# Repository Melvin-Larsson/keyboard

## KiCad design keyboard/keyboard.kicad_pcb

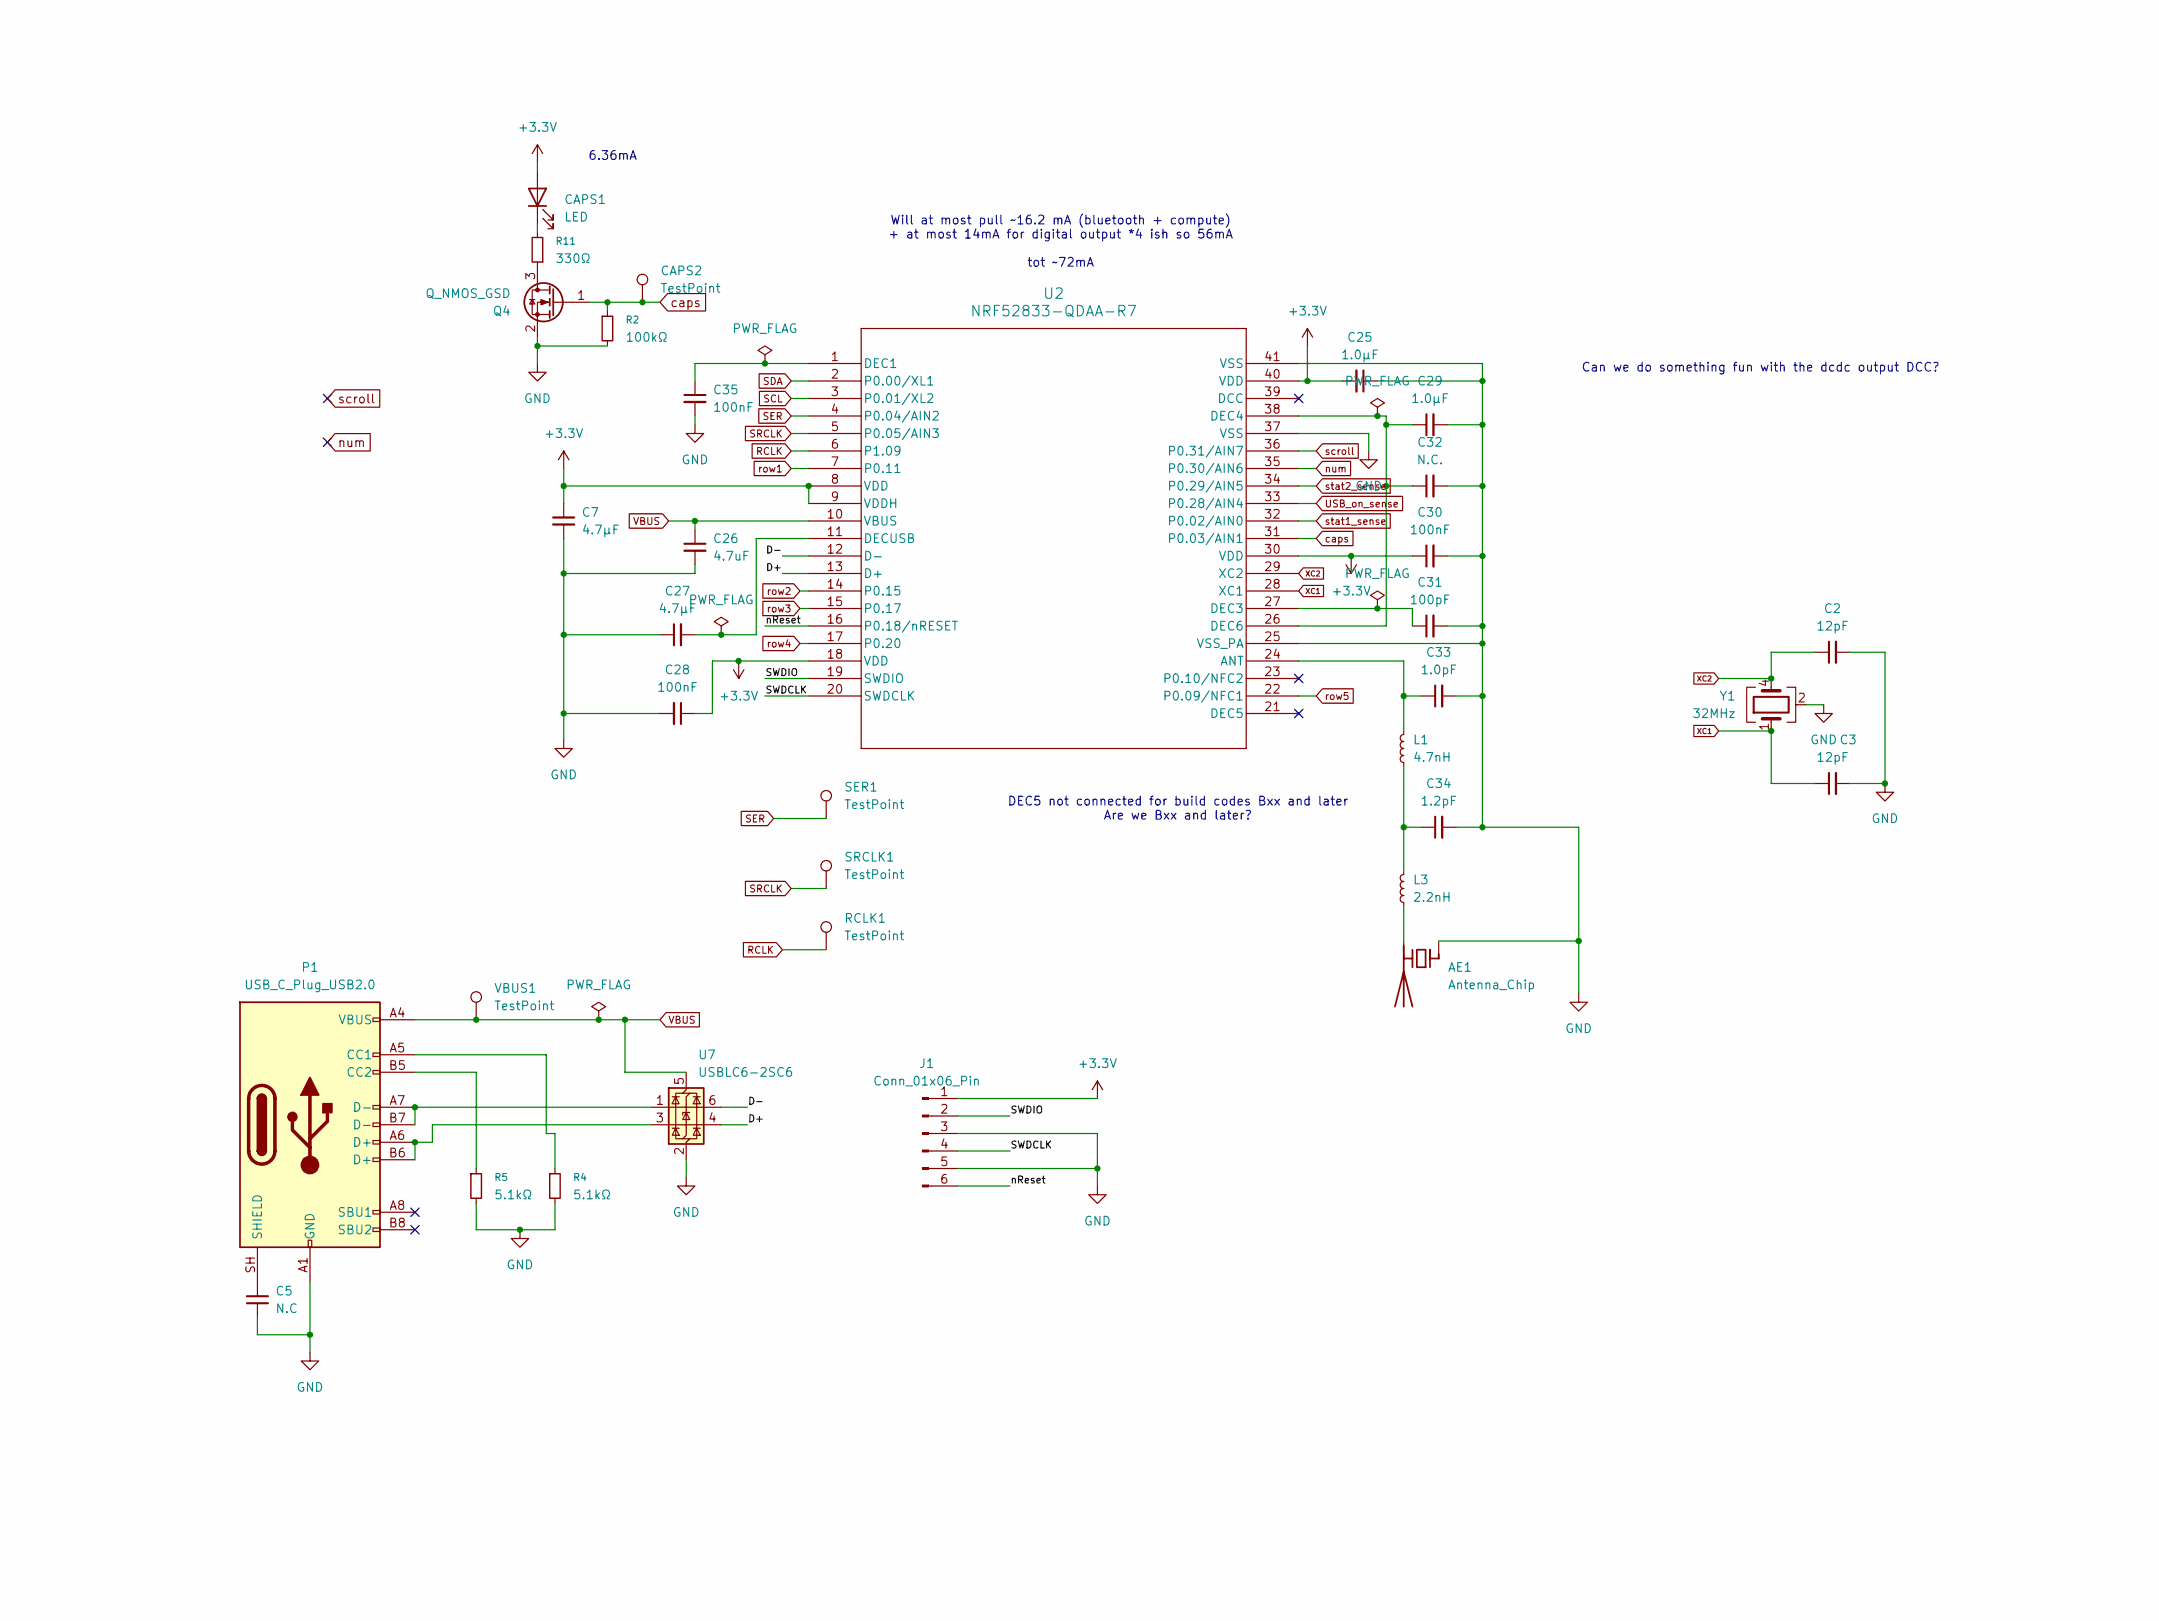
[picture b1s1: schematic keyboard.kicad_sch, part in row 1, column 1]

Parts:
AE1: Antenna_Chip; PCB-Antenna
C2, C3: 12pF; C_0201_0603Metric
C5: N.C; C_0603_1608Metric
C7, C27: 4.7μF; C_0603_1608Metric
C25, C29: 1.0μF; C_0402_1005Metric_small_silk
C26: 4.7uF; C_0603_1608Metric
C28, C30, C35: 100nF; C_0201_0603Metric
C31: 100pF; C_0201_0603Metric
C32: N.C.; C_0201_0603Metric
C33: 1.0pF; C_0201_0603Metric
C34: 1.2pF; C_0201_0603Metric
CAPS1: LED; LED_0603_1608Metric
CAPS2: TestPoint; TestPoint_THTPad_D2.0mm_Drill1.0mm_no_silk
J1: Conn_01x06_Pin; PinHeader_2x03_P2.54mm_Vertical
L1: 4.7nH; L_0201_0603Metric
L3: 2.2nH; L_0201_0603Metric
P1: USB_C_Plug_USB2.0; USB_C_Receptacle_G-Switch_GT-USB-7010ASV
Q4: Q_NMOS_GSD; SOT-23
R2: 100kΩ; R_0603_1608Metric
R4, R5: 5.1kΩ; R_0603_1608Metric
R11: 330Ω; R_0603_1608Metric
RCLK1: TestPoint; TestPoint_THTPad_D2.0mm_Drill1.0mm_no_silk
SER1: TestPoint; TestPoint_THTPad_D2.0mm_Drill1.0mm_no_silk
SRCLK1: TestPoint; TestPoint_THTPad_D2.0mm_Drill1.0mm_no_silk
U2: NRF52833-QDAA-R7; QFN40_5X5_DQ_NOR
U7: USBLC6-2SC6; SOT-23-6
VBUS1: TestPoint; TestPoint_THTPad_D2.0mm_Drill1.0mm_no_silk
Y1: 32MHz; Crystal_SMD_2016-4Pin_2.0x1.6mm

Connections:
+3.3V: C7.1, C25.2, C28.1, C30.1, CAPS1.2 (A), J1.1, U2.8 (VDD), U2.9 (VDDH), U2.18 (VDD), U2.30 (VDD), U2.40 (VDD); also elsewhere on the board
/D+: U2.13 (D+), U7.4 (I/O2)
/D-: U2.12 (D-), U7.6 (I/O1)
/SWDCLK: J1.4, U2.20 (SWDCLK)
/SWDIO: J1.2, U2.19 (SWDIO)
/nReset: J1.6, U2.16 (P0.18/nRESET)
GND: AE1.1 (FEED), C2.2, C3.2, C5.2, C7.2, C25.1, C26.2, C27.1, C28.2, C29.2, C30.2, C31.2, C32.2, C33.2, C34.2, C35.2, J1.3, J1.5, P1.A1 (GND), P1.A12 (GND), P1.B1 (GND), P1.B12 (GND), Q4.2 (S), R2.2, R4.2, R5.2, U2.25 (VSS_PA), U2.37 (VSS), U2.41 (VSS), U7.2 (GND), Y1.2 (G), Y1.3 (G); also elsewhere on the board
unnamed: AE1.2 (PCB_Trace), L3.1
unnamed: C34.1, L1.1, L3.2
unnamed: CAPS1.1 (K), R11.2
unnamed: P1.A5 (CC1), R4.1
unnamed: P1.B5 (CC2), R5.1
unnamed: P1.A6 (D+), P1.B6 (D+), U7.3 (I/O2)
unnamed: P1.A7 (D-), P1.B7 (D-), U7.1 (I/O1)
unnamed: C5.1, P1.SH (SHIELD)
unnamed: Q4.3 (D), R11.1
unnamed: C33.1, L1.2, U2.24 (ANT)
unnamed: C35.1, U2.1 (DEC1)
unnamed: C31.1, U2.27 (DEC3)
unnamed: C29.1, C32.1, U2.26 (DEC6), U2.38 (DEC4)
unnamed: C27.2, U2.11 (DECUSB)
RCLK: RCLK1.1 (1_1), U2.6 (P1.09); also elsewhere on the board
SCL: U2.3 (P0.01/XL2); also elsewhere on the board
SDA: U2.2 (P0.00/XL1); also elsewhere on the board
SER: SER1.1 (1_1), U2.4 (P0.04/AIN2); also elsewhere on the board
SRCLK: SRCLK1.1 (1_1), U2.5 (P0.05/AIN3); also elsewhere on the board
STAT1: U2.32 (P0.02/AIN0); also elsewhere on the board
STAT2: U2.34 (P0.29/AIN5); also elsewhere on the board
USBPG_N: U2.33 (P0.28/AIN4); also elsewhere on the board
VBUS: C26.1, P1.A4 (VBUS), P1.A9 (VBUS), P1.B4 (VBUS), P1.B9 (VBUS), U2.10 (VBUS), U7.5 (VBUS), VBUS1.1 (1_1); also elsewhere on the board
XC1: C3.1, U2.28 (XC1), Y1.1
XC2: C2.1, U2.29 (XC2), Y1.4
caps: CAPS2.1 (1_1), Q4.1 (G), R2.1, U2.31 (P0.03/AIN1)
num: U2.35 (P0.30/AIN6)
row1: U2.7 (P0.11); also elsewhere on the board
row2: U2.14 (P0.15); also elsewhere on the board
row3: U2.15 (P0.17); also elsewhere on the board
row4: U2.17 (P0.20); also elsewhere on the board
row5: U2.22 (P0.09/NFC1); also elsewhere on the board
scroll: U2.36 (P0.31/AIN7)

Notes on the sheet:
DEC5 not connected for build codes Bxx and later Are we Bxx and later?
Will at most pull ~16.2 mA (bluetooth + compute) + at most 14mA for digital output *4 ish so 56mA tot ~72mA
6.36mA
Can we do something fun with the dcdc output DCC?

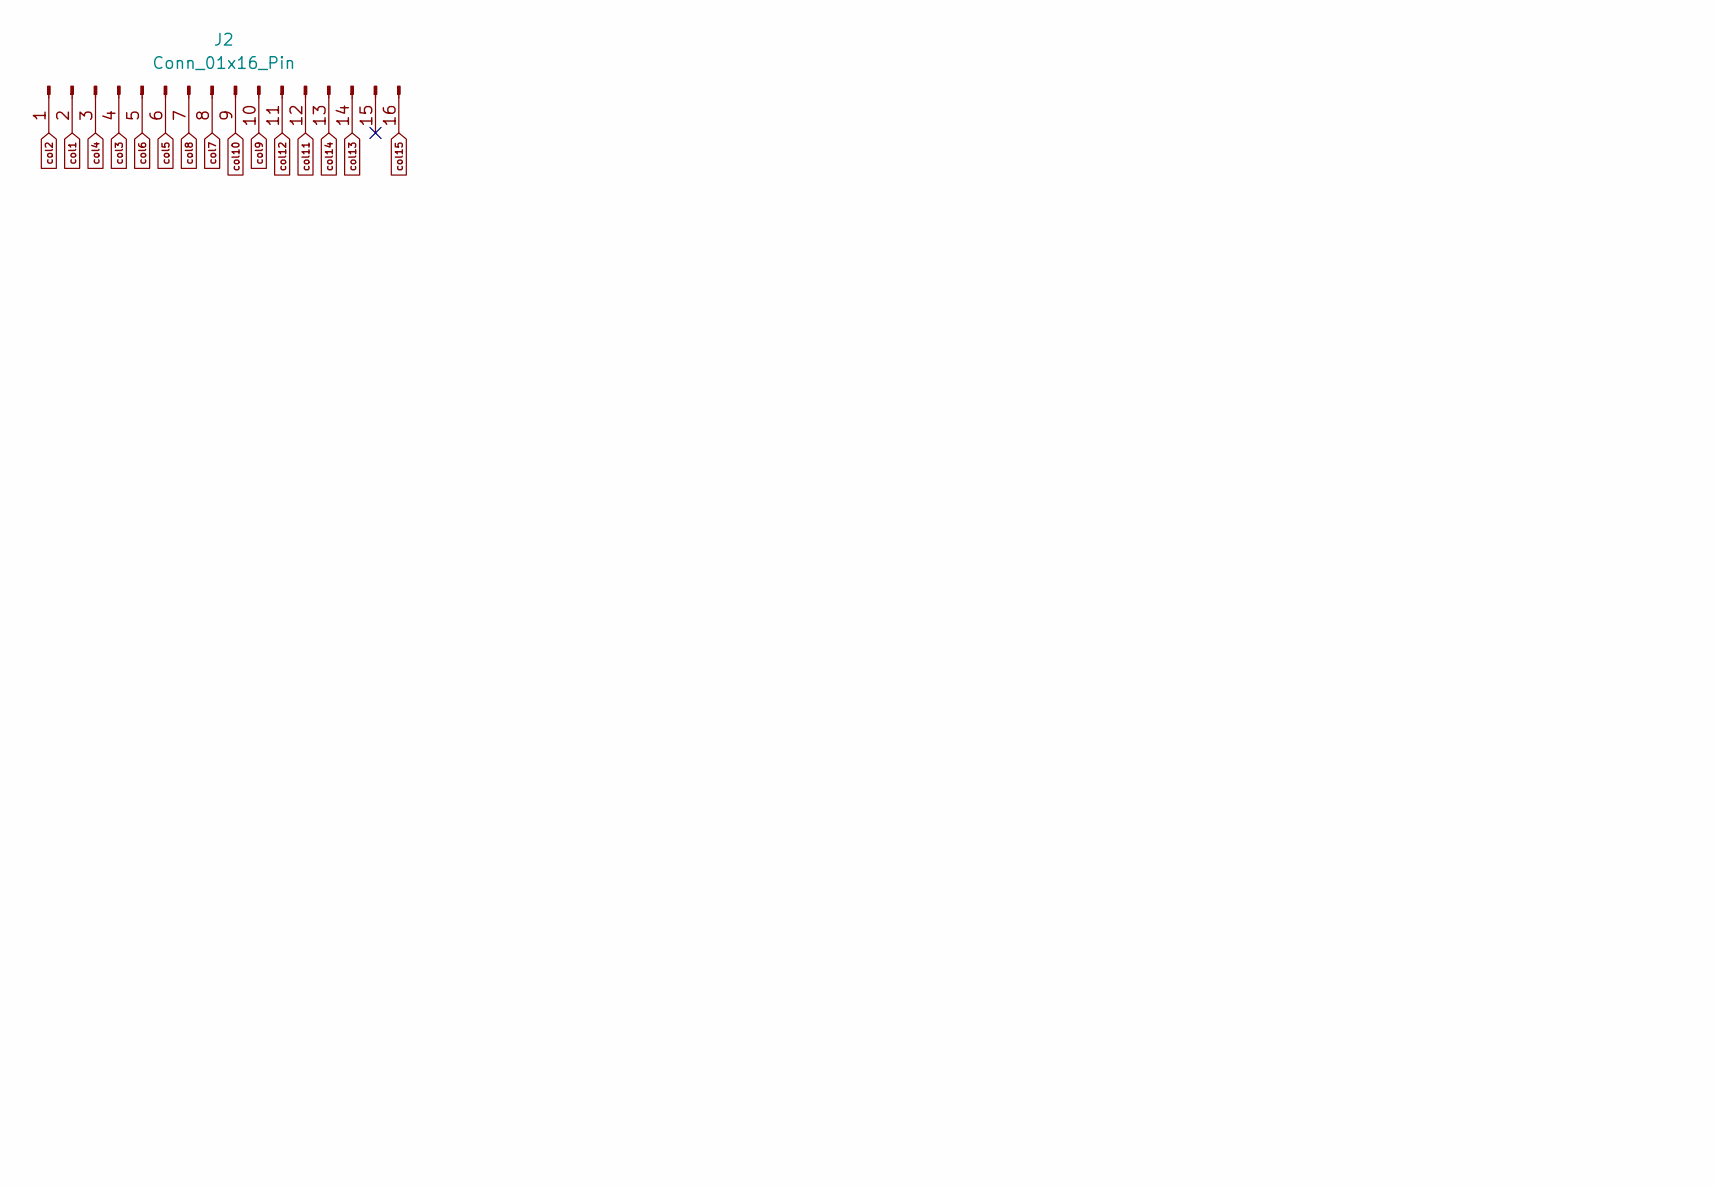
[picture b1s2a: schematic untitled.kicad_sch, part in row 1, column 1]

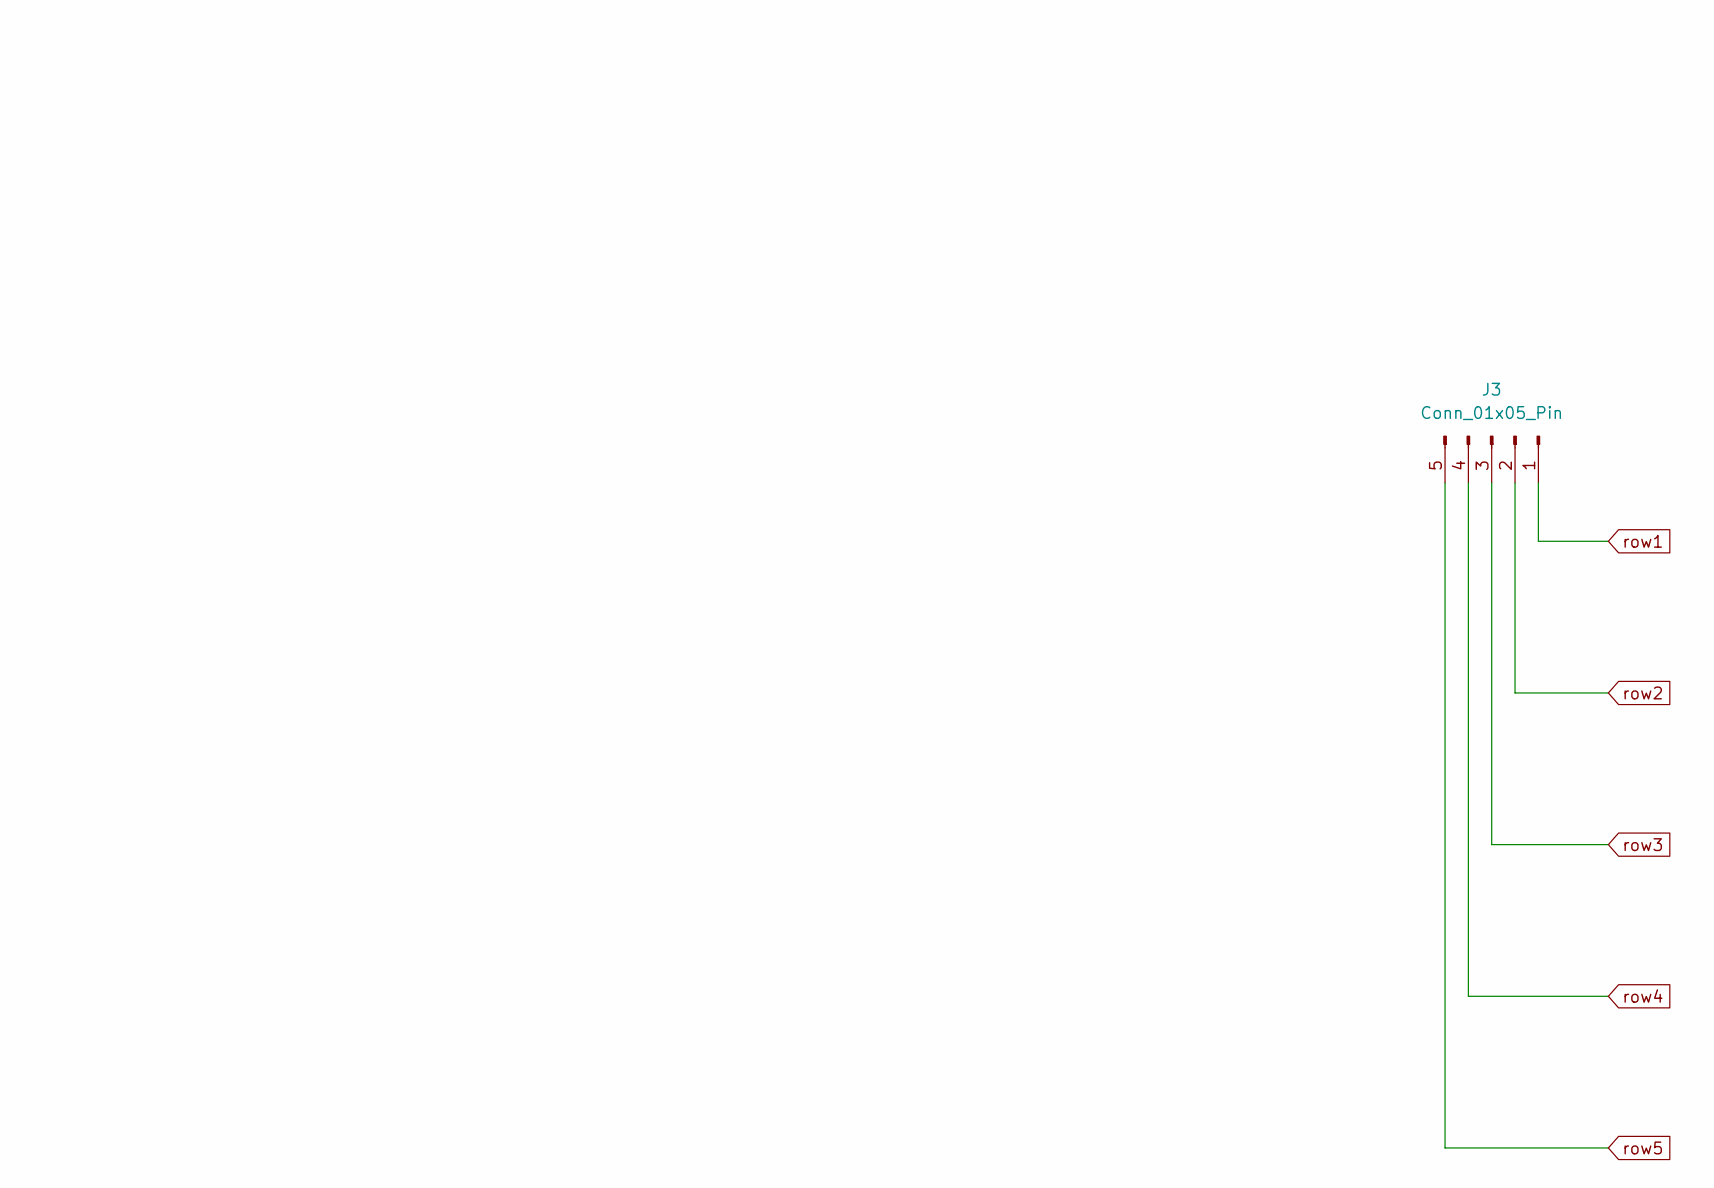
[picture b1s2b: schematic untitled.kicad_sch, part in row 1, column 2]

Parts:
J2: Conn_01x16_Pin; PinSocket_2x08_P2.54mm_Vertical
J3: Conn_01x05_Pin; PinSocket_1x05_P2.54mm_Vertical

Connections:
col1: J2.2; also elsewhere on the board
col2: J2.1; also elsewhere on the board
col3: J2.4; also elsewhere on the board
col4: J2.3; also elsewhere on the board
col5: J2.6; also elsewhere on the board
col6: J2.5; also elsewhere on the board
col7: J2.8; also elsewhere on the board
col8: J2.7; also elsewhere on the board
col9: J2.10; also elsewhere on the board
col10: J2.9; also elsewhere on the board
col11: J2.12; also elsewhere on the board
col12: J2.11; also elsewhere on the board
col13: J2.14; also elsewhere on the board
col14: J2.13; also elsewhere on the board
col15: J2.16; also elsewhere on the board
row1: J3.1; also elsewhere on the board
row2: J3.2; also elsewhere on the board
row3: J3.3; also elsewhere on the board
row4: J3.4; also elsewhere on the board
row5: J3.5; also elsewhere on the board

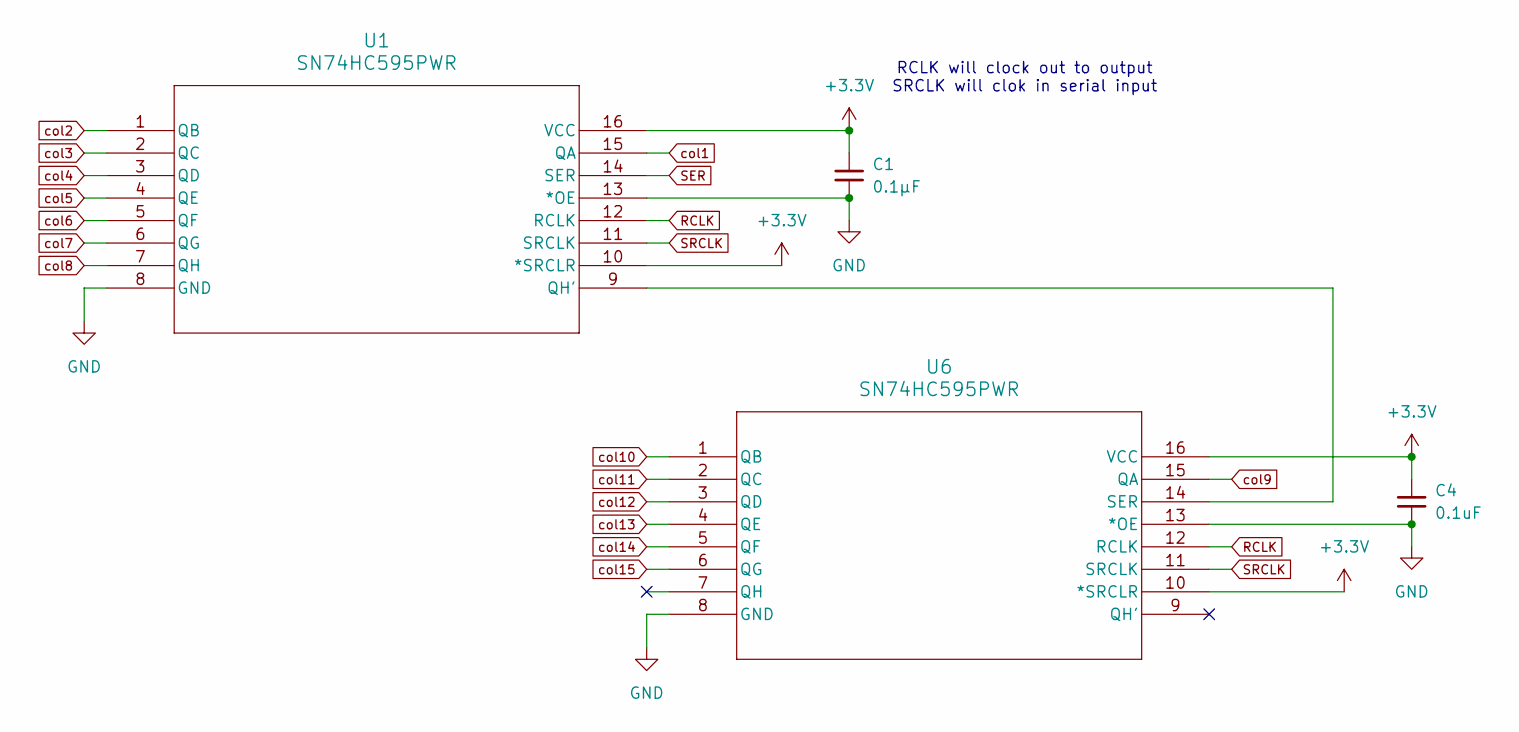
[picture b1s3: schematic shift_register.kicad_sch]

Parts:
C1: 0.1μF; C_0603_1608Metric
C4: 0.1uF; C_0603_1608Metric
U1, U6: SN74HC595PWR; PW16

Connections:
+3.3V: C1.1, C4.1, U1.10 (*SRCLR), U1.16 (VCC), U6.10 (*SRCLR), U6.16 (VCC); also elsewhere on the board
GND: C1.2, C4.2, U1.8 (GND), U1.13 (*OE), U6.8 (GND), U6.13 (*OE); also elsewhere on the board
unnamed: U1.9 (QH'), U6.14 (SER)
RCLK: U1.12 (RCLK), U6.12 (RCLK); also elsewhere on the board
SER: U1.14 (SER); also elsewhere on the board
SRCLK: U1.11 (SRCLK), U6.11 (SRCLK); also elsewhere on the board
col1: U1.15 (QA); also elsewhere on the board
col2: U1.1 (QB); also elsewhere on the board
col3: U1.2 (QC); also elsewhere on the board
col4: U1.3 (QD); also elsewhere on the board
col5: U1.4 (QE); also elsewhere on the board
col6: U1.5 (QF); also elsewhere on the board
col7: U1.6 (QG); also elsewhere on the board
col8: U1.7 (QH); also elsewhere on the board
col9: U6.15 (QA); also elsewhere on the board
col10: U6.1 (QB); also elsewhere on the board
col11: U6.2 (QC); also elsewhere on the board
col12: U6.3 (QD); also elsewhere on the board
col13: U6.4 (QE); also elsewhere on the board
col14: U6.5 (QF); also elsewhere on the board
col15: U6.6 (QG); also elsewhere on the board

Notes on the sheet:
RCLK will clock out to output SRCLK will clok in serial input

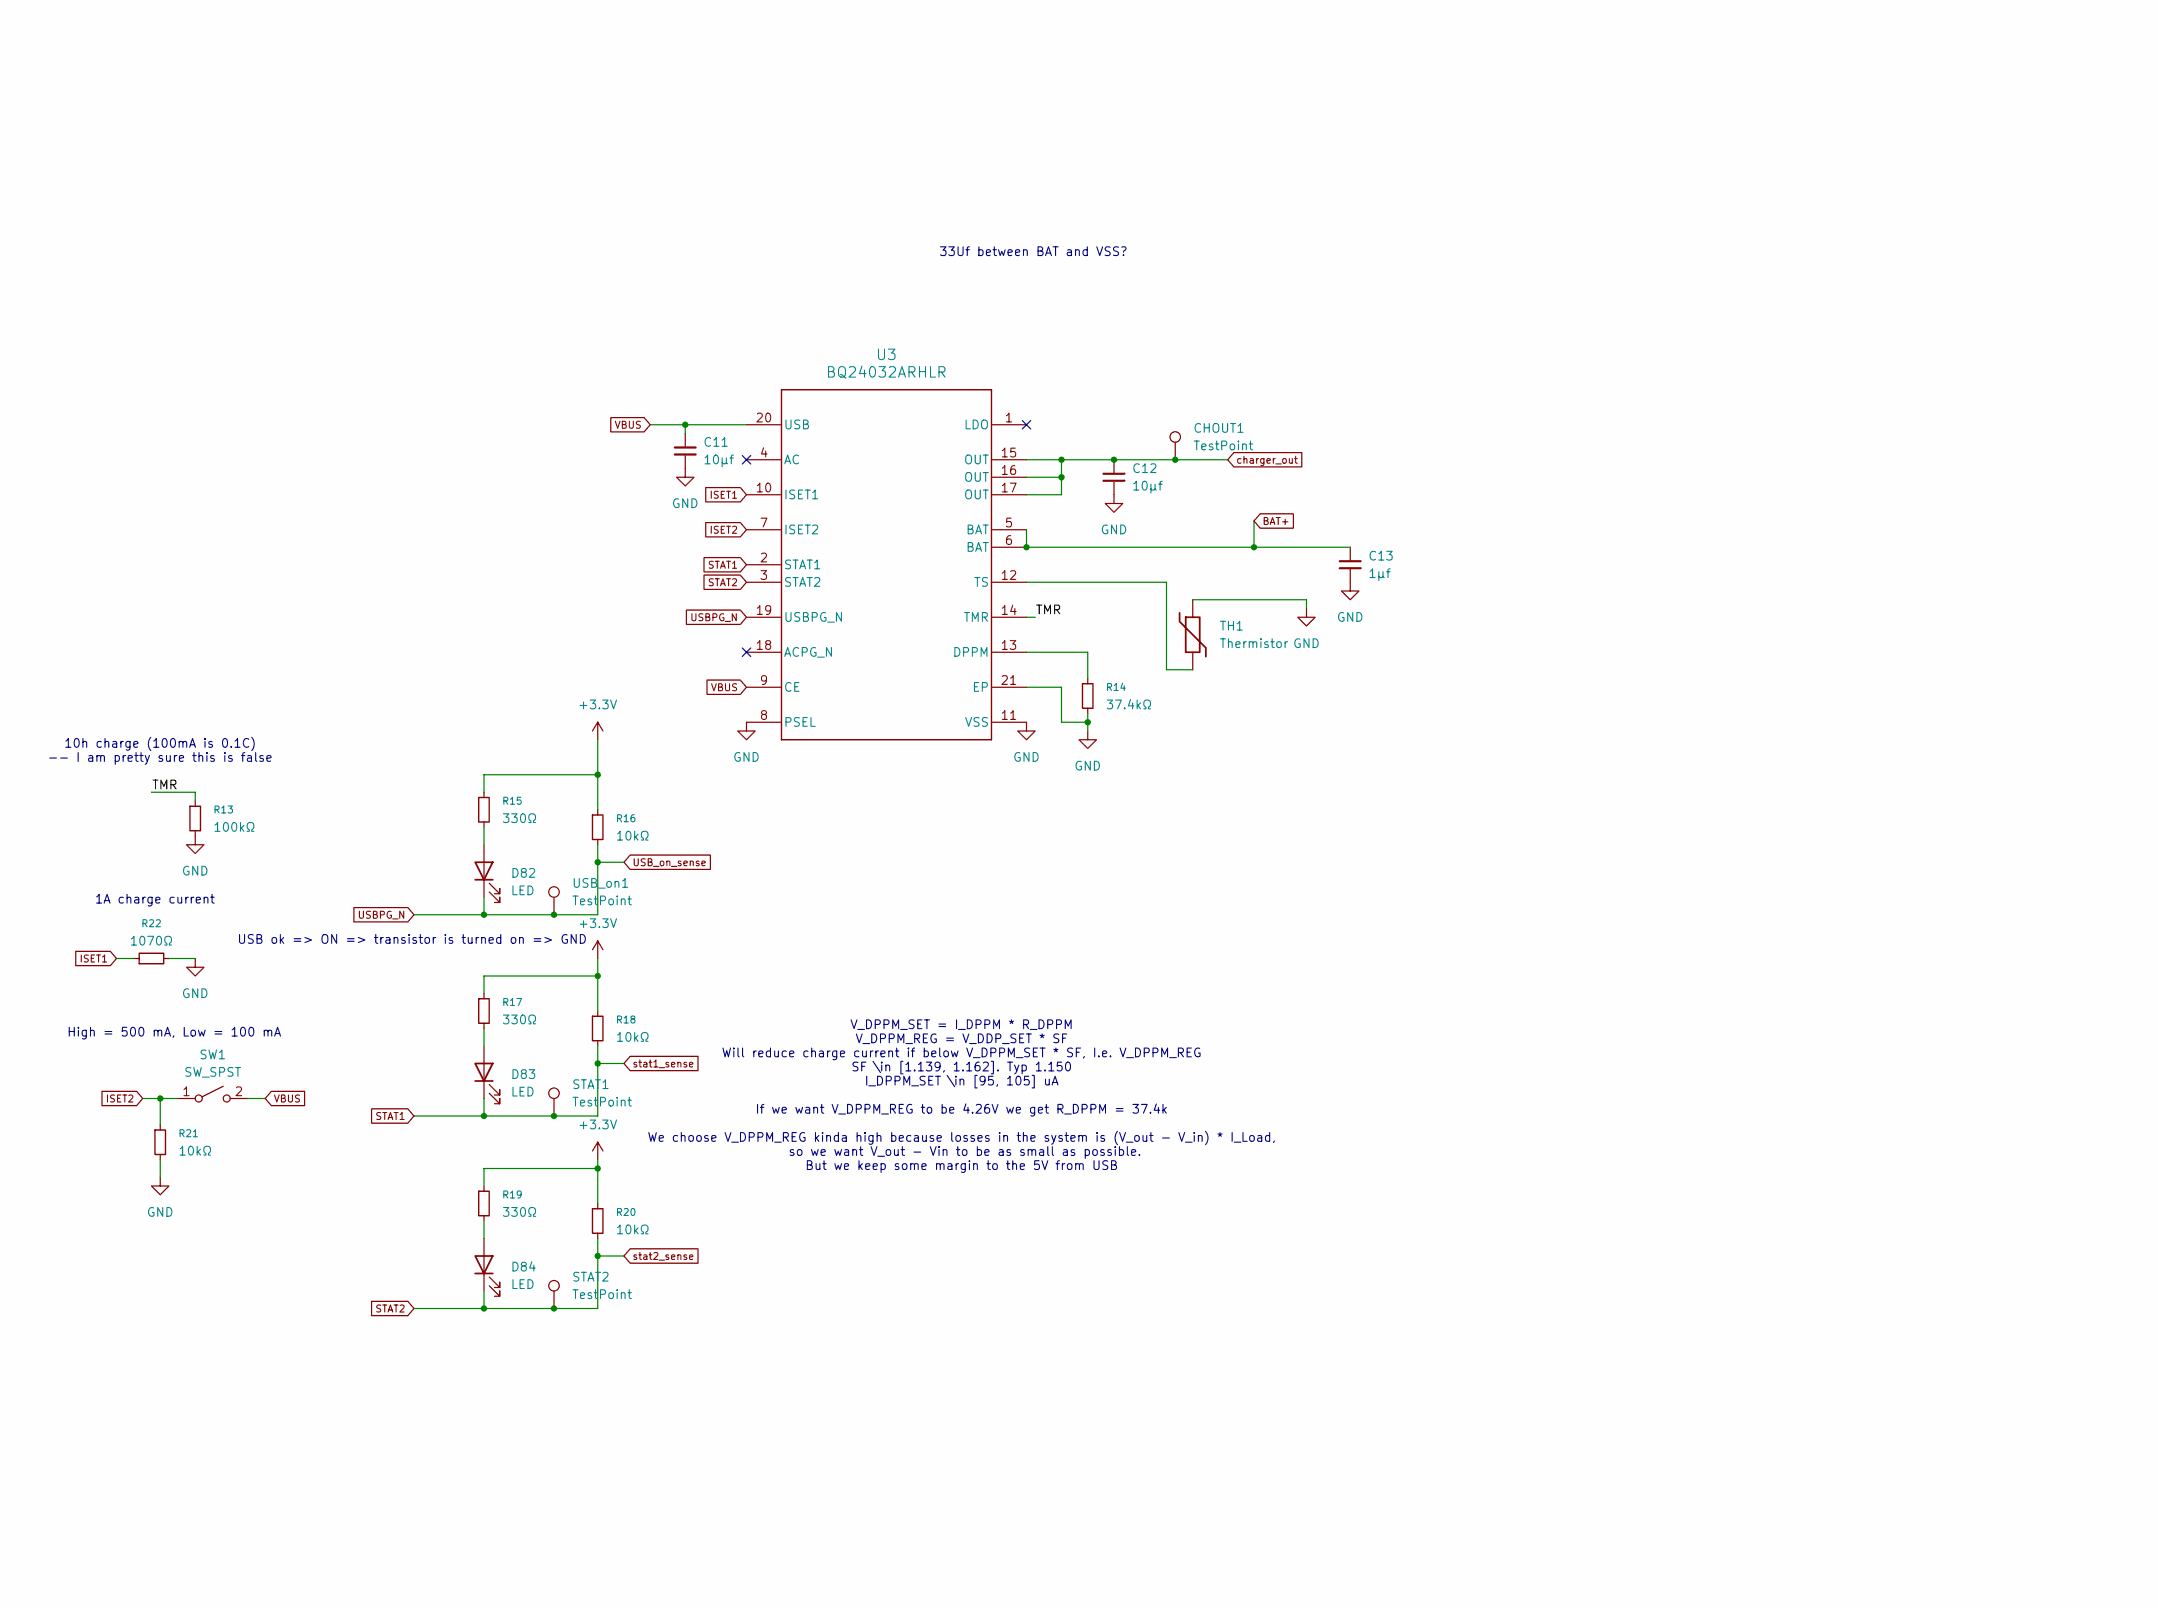
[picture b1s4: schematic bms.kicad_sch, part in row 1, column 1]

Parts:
C11, C12: 10μf; C_0805_2012Metric
C13: 1μf; C_0603_1608Metric
CHOUT1: TestPoint; TestPoint_THTPad_D2.0mm_Drill1.0mm_no_silk
D82, D83, D84: LED; LED_0603_1608Metric
R13: 100kΩ; R_0603_1608Metric
R14: 37.4kΩ; R_0603_1608Metric
R15, R17, R19: 330Ω; R_0603_1608Metric
R16, R18, R20, R21: 10kΩ; R_0603_1608Metric
R22: 1070Ω; R_0603_1608Metric
STAT1, STAT2: TestPoint; TestPoint_THTPad_D2.0mm_Drill1.0mm_no_silk
SW1: SW_SPST; SolderJumper-2_P1.3mm_Open_Pad1.0x1.5mm
TH1: Thermistor; solder_pads
U3: BQ24032ARHLR; RHL0020A
USB_on1: TestPoint; TestPoint_THTPad_D2.0mm_Drill1.0mm_no_silk

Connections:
+3.3V: R15.1, R16.1, R17.1, R18.1, R19.1, R20.1; also elsewhere on the board
/BMS/TMR: R13.1, U3.14 (TMR)
BAT+: C13.1, U3.5 (BAT), U3.6 (BAT); also elsewhere on the board
GND: C11.2, C12.2, C13.2, R13.2, R14.2, R21.2, R22.2, TH1.1, U3.8 (PSEL), U3.11 (VSS), U3.21 (EP); also elsewhere on the board
ISET1: R22.1, U3.10 (ISET1)
ISET2: R21.1, SW1.1 (A), U3.7 (ISET2)
unnamed: D82.2 (A), R15.2
unnamed: D83.2 (A), R17.2
unnamed: D84.2 (A), R19.2
unnamed: R14.1, U3.13 (DPPM)
unnamed: TH1.2, U3.12 (TS)
STAT1: D83.1 (K), R18.2, STAT1.1 (1_1), U3.2 (STAT1); also elsewhere on the board
STAT2: D84.1 (K), R20.2, STAT2.1 (1_1), U3.3 (STAT2); also elsewhere on the board
USBPG_N: D82.1 (K), R16.2, U3.19 (USBPG_N), USB_on1.1 (1_1); also elsewhere on the board
VBUS: C11.1, SW1.2 (B), U3.9 (CE), U3.20 (USB); also elsewhere on the board
charger_out: C12.1, CHOUT1.1 (1_1), U3.15 (OUT), U3.16 (OUT), U3.17 (OUT); also elsewhere on the board

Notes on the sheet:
33Uf between BAT and VSS?
10h charge (100mA is 0.1C) -- I am pretty sure this is false
USB ok => ON => transistor is turned on => GND
V_DPPM_SET = I_DPPM * R_DPPM V_DPPM_REG = V_DDP_SET * SF Will reduce charge current if below V_DPPM_SET * SF, I.e. V_DPPM_REG SF \in [1.139, 1.162]. Typ 1.150 I_DPPM_SET \in [95, 105] uA If we want V_DPPM_REG to be 4.26V we get R_DPPM = 37.4k We choose V_DPPM_REG kinda high because losses in the sy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
High = 500 mA, Low = 100 mA
1A charge current

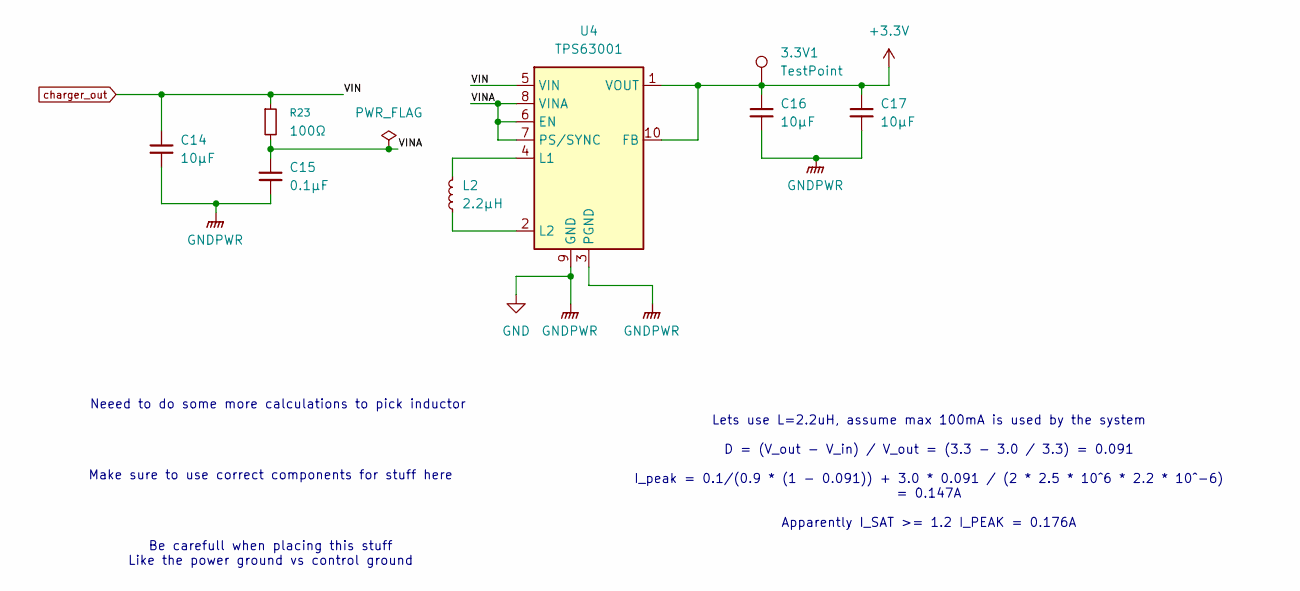
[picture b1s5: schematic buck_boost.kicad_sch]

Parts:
3.3V1: TestPoint; TestPoint_THTPad_D2.0mm_Drill1.0mm_no_silk
C14, C16, C17: 10μF; C_0805_2012Metric
C15: 0.1μF; C_0603_1608Metric
L2: 2.2μH; IND_LQH3NPN2R2MJRL
R23: 100Ω; R_0603_1608Metric
U4: TPS63001

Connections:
+3.3V: 3.3V1.1 (1_1), C16.1, C17.1, U4.1 (VOUT), U4.10 (FB); also elsewhere on the board
/BMS/buck_boost/VINA: C15.1, R23.2, U4.6 (EN), U4.7 (PS/SYNC), U4.8 (VINA)
GND: C14.2, C15.2, C16.2, C17.2, U4.3 (PGND), U4.9 (GND), U4.11 (PGND); also elsewhere on the board
unnamed: L2.2, U4.4 (L1)
unnamed: L2.1, U4.2 (L2)
charger_out: C14.1, R23.1, U4.5 (VIN); also elsewhere on the board

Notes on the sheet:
Lets use L=2.2uH, assume max 100mA is used by the system D = (V_out - V_in) / V_out = (3.3 - 3.0 / 3.3) = 0.091 I_peak = 0.1/(0.9 * (1 - 0.091)) + 3.0 * 0.091 / (2 * 2.5 * 10^6 * 2.2 * 10^-6) = 0.147A Apparently I_SAT >= 1.2 I_PEAK = 0.176A
Neeed to do some more calculations to pick inductor
Make sure to use correct components for stuff here
Be carefull when placing this stuff Like the power ground vs control ground

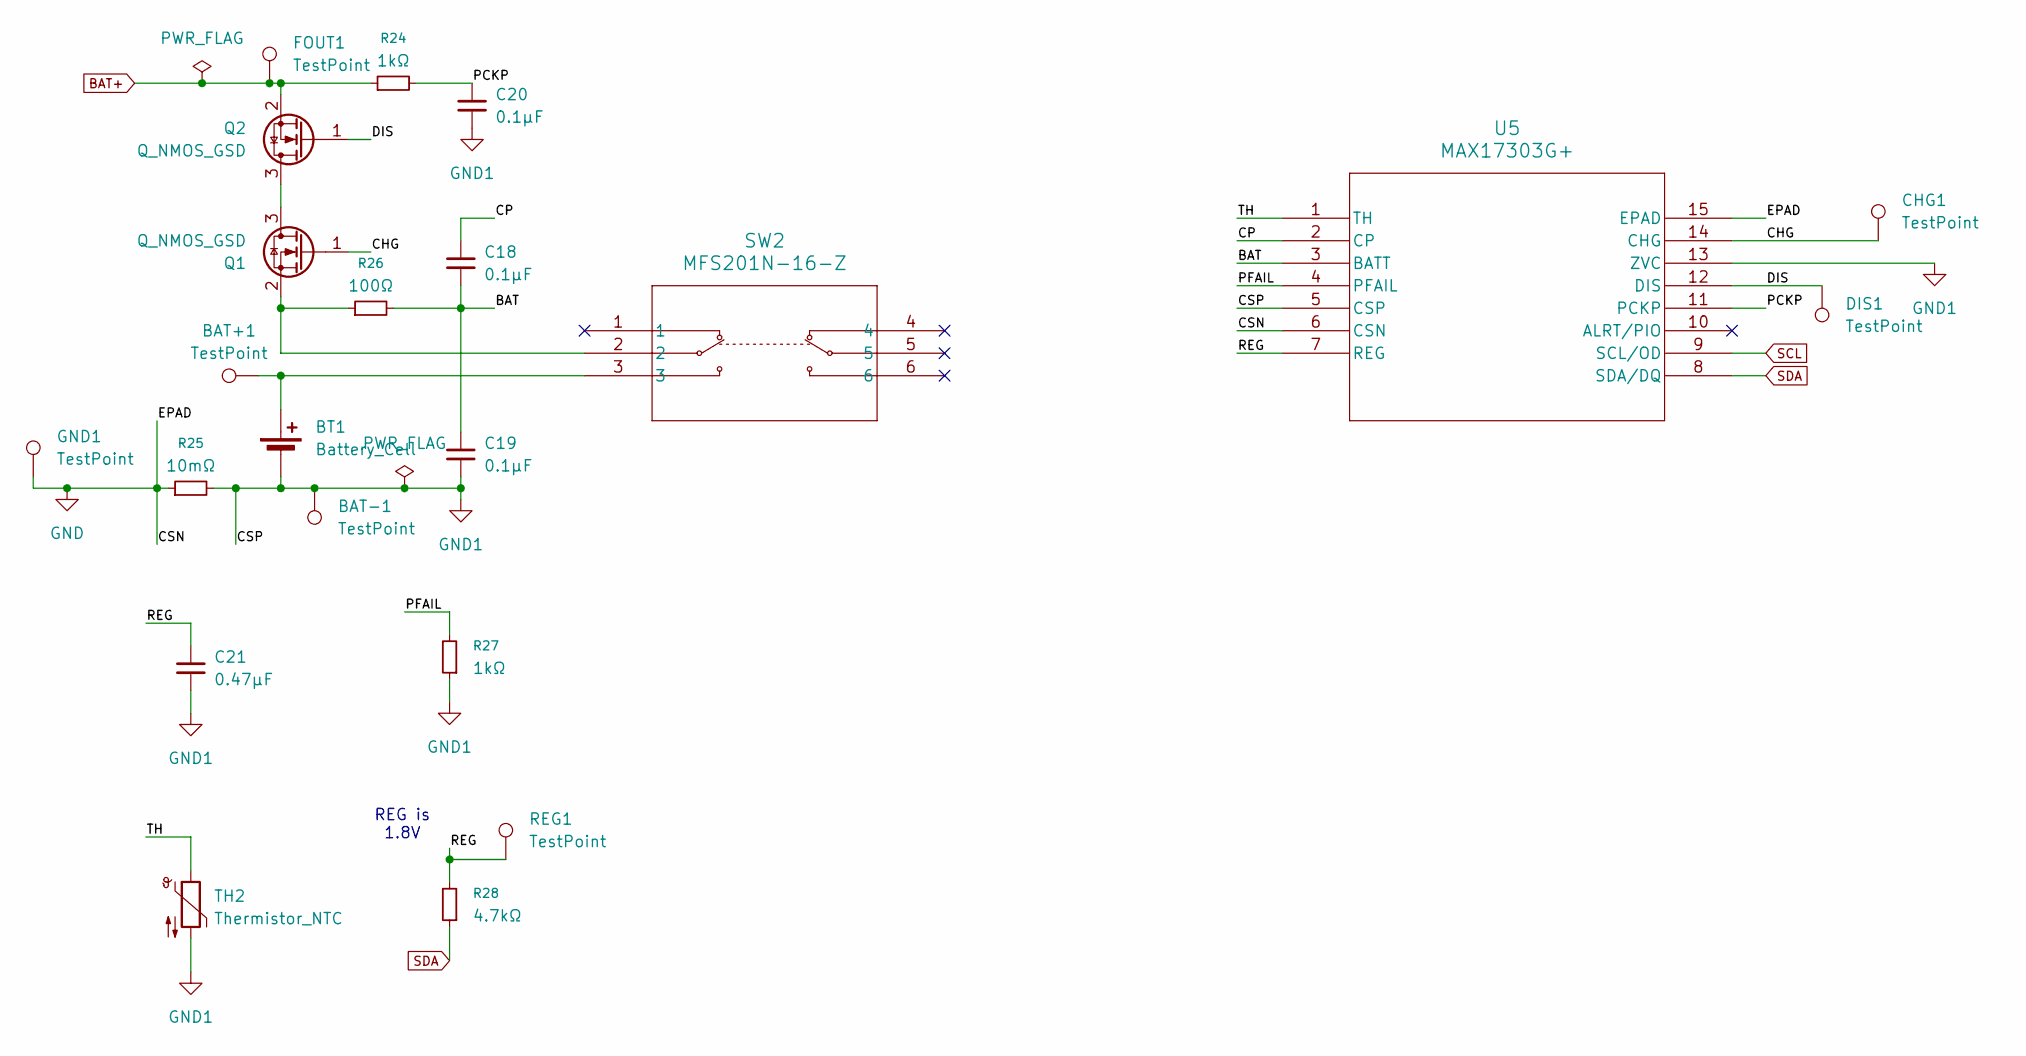
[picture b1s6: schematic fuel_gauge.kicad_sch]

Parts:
BAT+1: TestPoint; TestPoint_THTPad_D2.0mm_Drill1.0mm_no_silk
BAT-1: TestPoint; TestPoint_THTPad_D2.0mm_Drill1.0mm_no_silk
BT1: Battery_Cell; solder_pads
C18, C19, C20: 0.1μF; C_0603_1608Metric
C21: 0.47μF; C_0603_1608Metric
CHG1: TestPoint; TestPoint_THTPad_D2.0mm_Drill1.0mm_no_silk
DIS1: TestPoint; TestPoint_THTPad_D2.0mm_Drill1.0mm_no_silk
FOUT1: TestPoint; TestPoint_THTPad_D2.0mm_Drill1.0mm_no_silk
GND1: TestPoint; TestPoint_THTPad_D2.0mm_Drill1.0mm_no_silk
Q1, Q2: Q_NMOS_GSD; SOT-23
R24, R27: 1kΩ; R_0603_1608Metric
R25: 10mΩ; R_0603_1608Metric
R26: 100Ω; R_0603_1608Metric
R28: 4.7kΩ; R_0603_1608Metric
REG1: TestPoint; TestPoint_THTPad_D2.0mm_Drill1.0mm_no_silk
SW2: MFS201N-16-Z; MFS201N-16-Z_NDC
TH2: Thermistor_NTC; solder_pads
U5: MAX17303G+; 21-0137I_T1433-2_MXM

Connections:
/BMS/Fuel gauge/BAT: C18.2, C19.1, R26.2, U5.3 (BATT)
/BMS/Fuel gauge/CHG: CHG1.1 (1_1), Q1.1 (G), U5.14 (CHG)
/BMS/Fuel gauge/CP: C18.1, U5.2 (CP)
/BMS/Fuel gauge/DIS: DIS1.1 (1_1), Q2.1 (G), U5.12 (DIS)
/BMS/Fuel gauge/PCKP: C20.1, R24.2, U5.11 (PCKP)
/BMS/Fuel gauge/PFAIL: R27.2, U5.4 (PFAIL)
/BMS/Fuel gauge/REG: C21.1, R28.2, REG1.1 (1_1), U5.7 (REG)
/BMS/Fuel gauge/TH: TH2.1, U5.1 (TH)
BAT+: FOUT1.1 (1_1), Q2.2 (S), R24.1; also elsewhere on the board
GND: GND1.1 (1_1), R25.1, U5.6 (CSN), U5.15 (EPAD); also elsewhere on the board
GND1: BAT-1.1 (1_1), BT1.2 (-), C19.2, C20.2, C21.2, R25.2, R27.1, TH2.2, U5.5 (CSP), U5.13 (ZVC)
unnamed: BAT+1.1 (1_1), BT1.1 (+), SW2.3
unnamed: Q1.3 (D), Q2.3 (D)
unnamed: Q1.2 (S), R26.1, SW2.2
SCL: U5.9 (SCL/OD); also elsewhere on the board
SDA: R28.1, U5.8 (SDA/DQ); also elsewhere on the board

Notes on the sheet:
REG is 1.8V

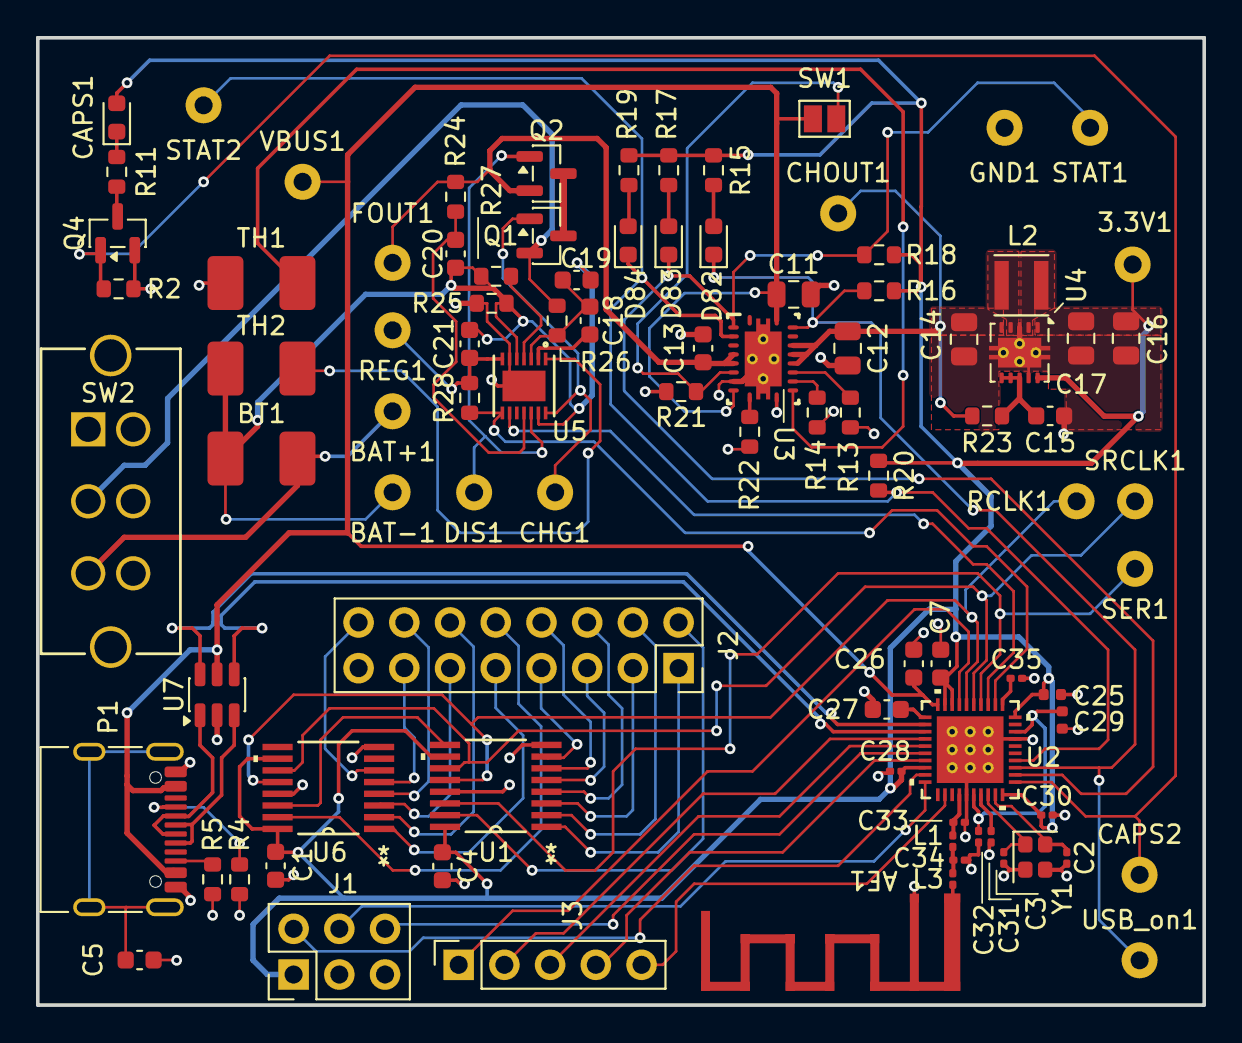
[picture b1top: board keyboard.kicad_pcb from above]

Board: 4 copper layers, 64.8 x 53.7 mm, 93 parts (0 on the bottom side), 79 nets.
